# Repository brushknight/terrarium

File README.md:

# Terrarium Controller

It consists of 2 parts, IoT esp32 based controller and server that works as a proxy for other data storages.

[DHT22 case 3D model](https://www.prusaprinters.org/prints/77052-dht22-case), [Controller enclosure](https://www.prusaprinters.org/prints/77143-terrarium-controller-enclosure)

This is example of Home Assistant dashboard built for 3 terrariums that we own.

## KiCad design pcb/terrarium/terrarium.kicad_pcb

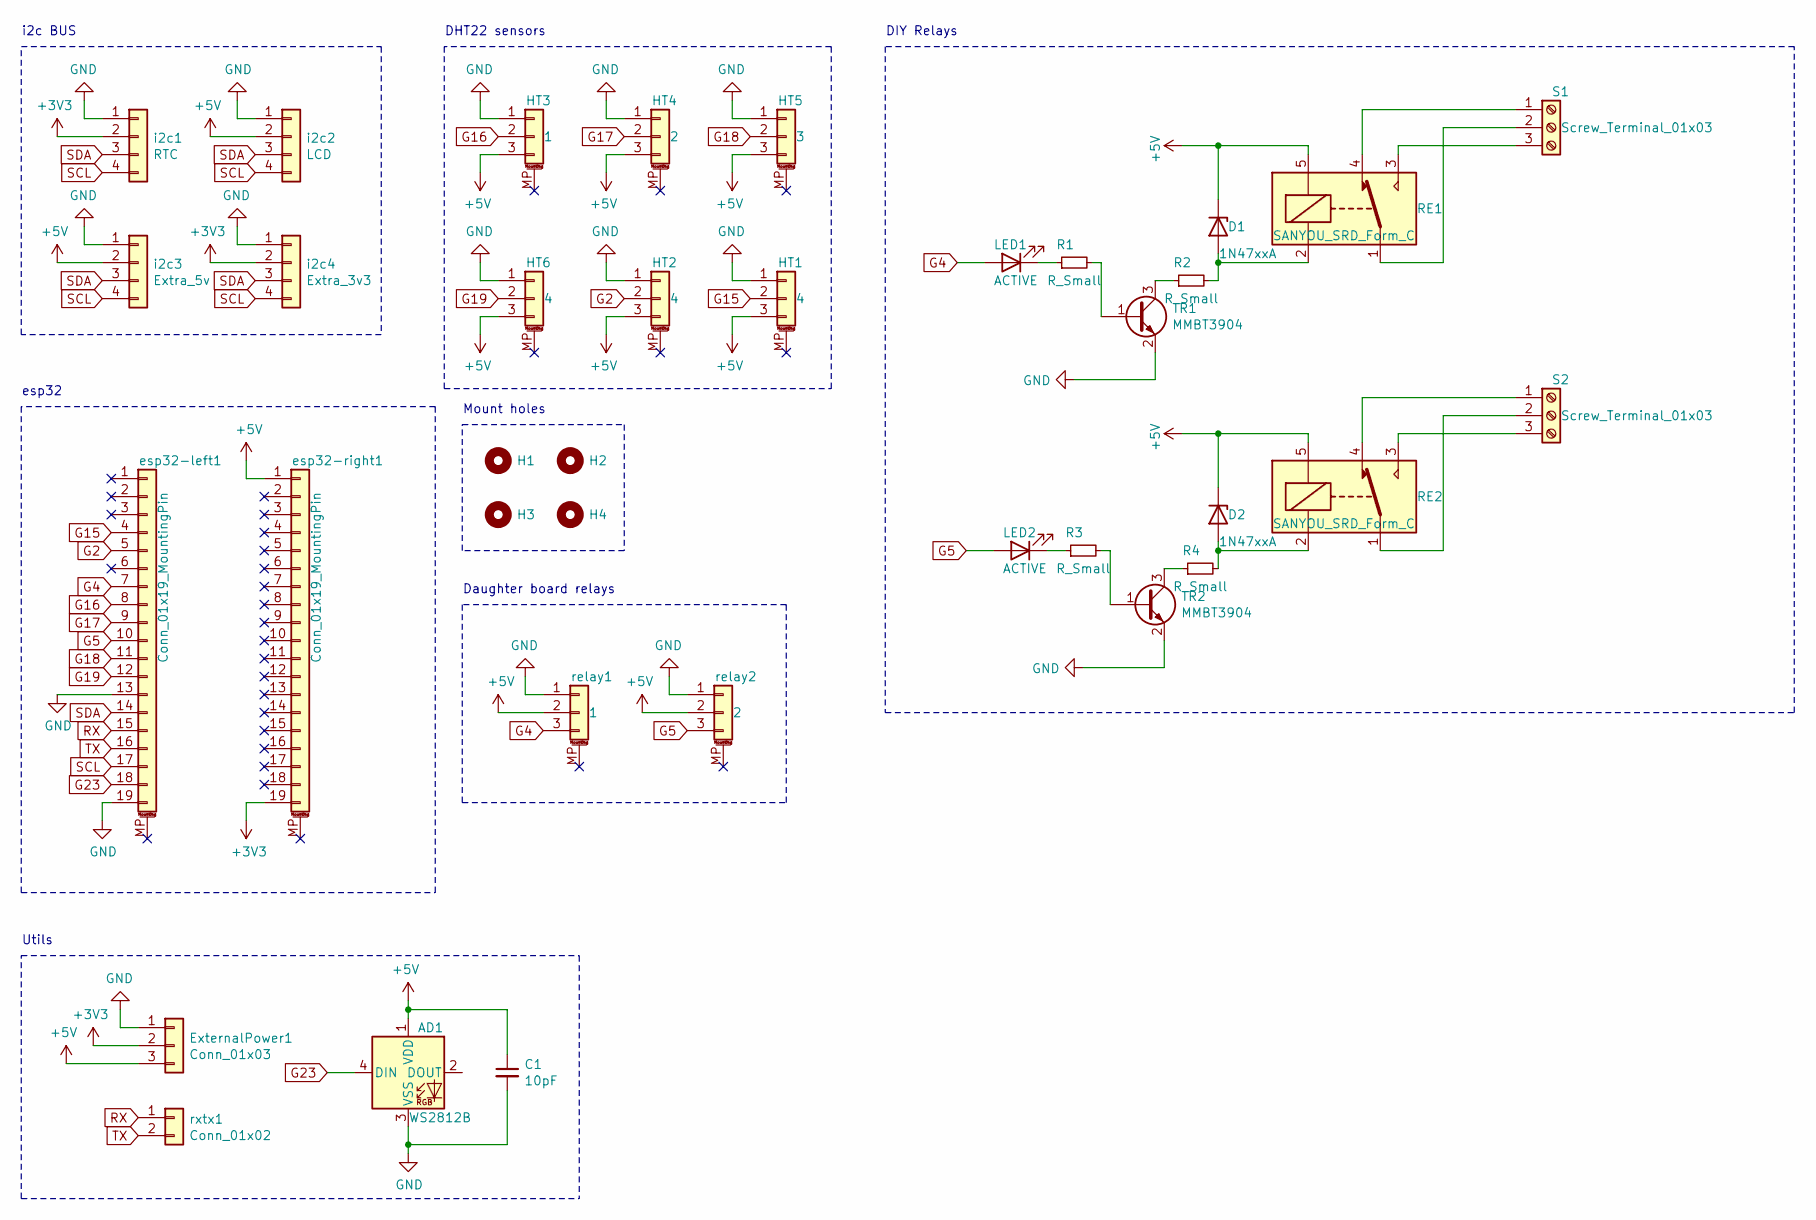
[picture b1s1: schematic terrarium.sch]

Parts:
AD1: WS2812B; LED_WS2812B_PLCC4_5.0x5.0mm_P3.2mm
C1: 10pF; C_Disc_D5.0mm_W2.5mm_P5.00mm
D1, D2: 1N47xxA; D_DO-41_SOD81_P7.62mm_Horizontal
ExternalPower1: Conn_01x03; PinHeader_1x03_P2.54mm_Vertical
H1, H2, H3, H4: MountingHole; MountingHole_3.2mm_M3_DIN965_Pad
HT1, HT2, HT6: 4; JST_XH_B3B-XH-AM_1x03_P2.50mm_Vertical
HT3: 1; JST_XH_B3B-XH-AM_1x03_P2.50mm_Vertical
HT4: 2; JST_XH_B3B-XH-AM_1x03_P2.50mm_Vertical
HT5: 3; JST_XH_B3B-XH-AM_1x03_P2.50mm_Vertical
LED1, LED2: ACTIVE; LED_D3.0mm_Clear
R1, R2, R3, R4: R_Small; R_Axial_DIN0204_L3.6mm_D1.6mm_P2.54mm_Vertical
RE1, RE2: SANYOU_SRD_Form_C; Relay_SPDT_SANYOU_SRD_Series_Form_C
S1, S2: Screw_Terminal_01x03; TerminalBlock_bornier-3_P5.08mm
TR1, TR2: MMBT3904; TO-92
esp32-left1, esp32-right1: Conn_01x19_MountingPin; PinHeader_1x19_P2.54mm_Vertical
i2c1: RTC; PinHeader_1x04_P2.54mm_Vertical
i2c2: LCD; JST_XH_B4B-XH-AM_1x04_P2.50mm_Vertical
i2c3: Extra_5v; PinHeader_1x04_P2.54mm_Vertical
i2c4: Extra_3v3; PinHeader_1x04_P2.54mm_Vertical
relay1: 1; PinHeader_1x03_P2.54mm_Vertical
relay2: 2; PinHeader_1x03_P2.54mm_Vertical
rxtx1: Conn_01x02; PinSocket_1x02_P2.54mm_Vertical

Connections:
+3V3: ExternalPower1.2, esp32-right1.19, i2c1.2, i2c4.2
+5V: AD1.1 (VDD), C1.1, D1.1 (K), D2.1 (K), ExternalPower1.3, HT1.3, HT2.3, HT3.3, HT4.3, HT5.3, HT6.3, RE1.5, RE2.5, esp32-right1.1, i2c2.2, i2c3.2, relay1.2, relay2.2
G2: HT2.2, esp32-left1.5
G4: LED1.2 (A), esp32-left1.7, relay1.3
G5: LED2.2 (A), esp32-left1.10, relay2.3
G15: HT1.2, esp32-left1.4
G16: HT3.2, esp32-left1.8
G17: HT4.2, esp32-left1.9
G18: HT5.2, esp32-left1.11
G19: HT6.2, esp32-left1.12
G23: AD1.4 (DIN), esp32-left1.18
GND: AD1.3 (VSS), C1.2, ExternalPower1.1, HT1.1, HT2.1, HT3.1, HT4.1, HT5.1, HT6.1, TR1.2 (E), TR2.2 (E), esp32-left1.13, esp32-left1.19, i2c1.1, i2c2.1, i2c3.1, i2c4.1, relay1.1, relay2.1
unnamed: D1.2 (A), R2.2, RE1.2
unnamed: D2.2 (A), R4.2, RE2.2
unnamed: LED1.1 (K), R1.1
unnamed: LED2.1 (K), R3.1
unnamed: R1.2, TR1.1 (B)
unnamed: R2.1, TR1.3 (C)
unnamed: R3.2, TR2.1 (B)
unnamed: R4.1, TR2.3 (C)
unnamed: RE1.1, S1.2
unnamed: RE1.3, S1.3
unnamed: RE1.4, S1.1
unnamed: RE2.1, S2.2
unnamed: RE2.3, S2.3
unnamed: RE2.4, S2.1
RX: esp32-left1.15, rxtx1.1
SCL: esp32-left1.17, i2c1.4, i2c2.4, i2c3.4, i2c4.4
SDA: esp32-left1.14, i2c1.3, i2c2.3, i2c3.3, i2c4.3
TX: esp32-left1.16, rxtx1.2

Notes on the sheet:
DHT22 sensors
i2c BUS
esp32
Mount holes
DIY Relays
Daughter board relays
Utils

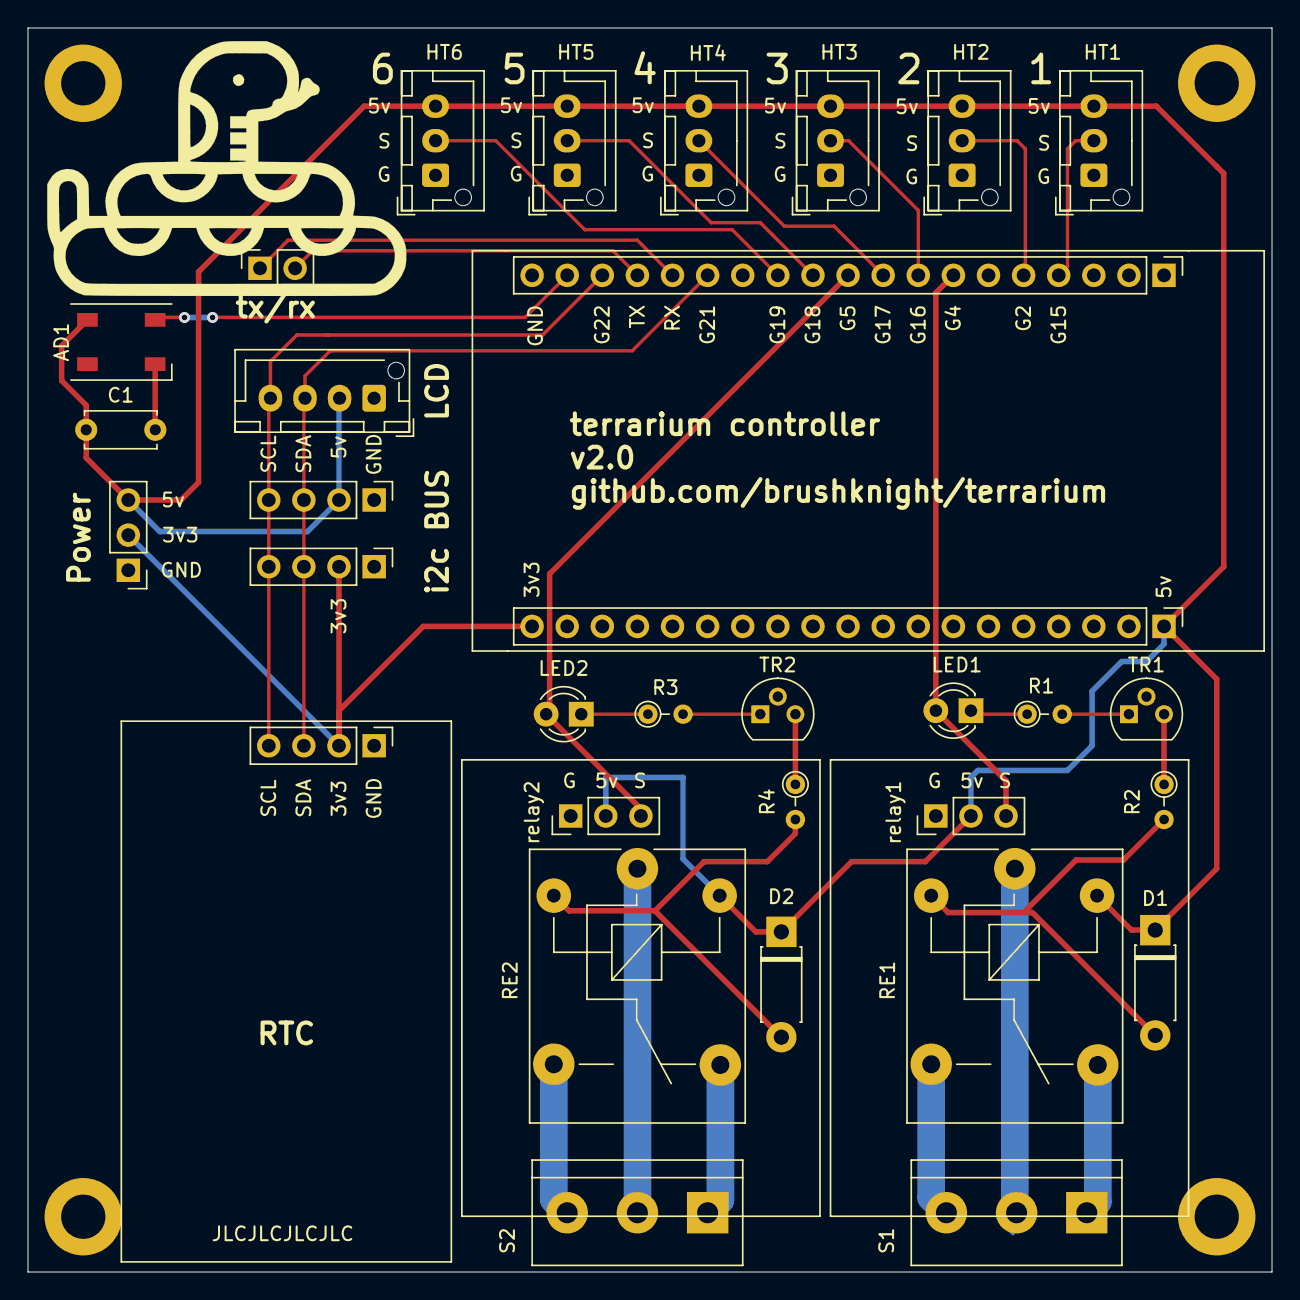
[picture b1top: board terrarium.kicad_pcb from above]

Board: 2 copper layers, 90.0 x 90.0 mm, 36 parts (0 on the bottom side), 30 nets.

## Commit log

2021-04-15 wip: Setup DHT22 and hall sensors
2021-04-19 feat: split files & add climate control
2021-05-09 fix: adjusted temp sensors pin for the latest circuit
2021-05-13 feat: add Wifi & NTP
2021-05-14 feat: add time into heating schedule
2021-05-16 feat: add server and telemetry send
2021-05-16 ci: add docker build
2021-05-16 ci: rename image
2021-05-16 fix: change port of go server to 80
2021-05-17 feat: add heating phases to build better heating window
2021-05-18 feat: add heater phase telemetry
2021-05-18 fix: add cold/warm temp tolerance split
2021-08-01 feat: update temp range
2021-08-28 wip: setting up lcd
2021-08-30 wip: RTC setup
2021-08-31 print time
2021-09-01 update display
2021-09-01 add encoder support
2021-09-16 update screen & config
2021-09-20 fix display
2021-09-23 add display object
2021-09-23 make wifi required only for initial time sync
2021-09-23 server: add support for multiple terrariums
2021-09-23 feat: add telemetry submission
2021-09-23 fix response encoding
2021-09-24 docs: add readme
2021-09-24 docs: update readme
2021-09-26 minor updates and fixes
2021-09-29 feat: add more system telemetry
2021-09-29 fix: bug with system sample
2021-09-29 fix: add debug for esp, fix sample in server
2021-11-06 pcb draft
2021-11-06 pcb v1.0
2021-11-06 updated PCB
2021-11-07 add support for old pcb, add final changes to pcb
2021-11-07 add gerber files
2021-11-12 wip: relay scheme
2021-11-12 wip: re-do pcb, add relay
2021-11-14 wip: update pcb
2021-11-17 wip: pcb relay design
2021-11-18 wip: finish with pcb layout
2021-11-18 wip: polish pcb
2021-11-18 fix: gnd connectivity for TR1
2021-11-18 fix: bug with RE2 terminal
2021-11-19 pcb: add ws2812b
2021-11-20 pcb minor changes
2021-11-24 wip: 2 relay heating
2021-11-25 wip: updating code to work with 2 heat zones
2021-11-26 fix screen for 2 relays
2021-12-02 migrated hardware to dedicated repo
2021-12-21 add freeRTOS
2021-12-22 add webserver
2021-12-22 update prom endpoint
2021-12-29 update DHT22 library
2022-01-21 wip RTC
2022-01-22 RTC: sync only on boot
2022-01-22 fix rtc
2022-01-29 feat: updated climate control part
2022-01-29 setup working prom endpoint
2022-01-30 working on endpoint
2022-02-19 fix bugs
2022-04-12 add submodules
